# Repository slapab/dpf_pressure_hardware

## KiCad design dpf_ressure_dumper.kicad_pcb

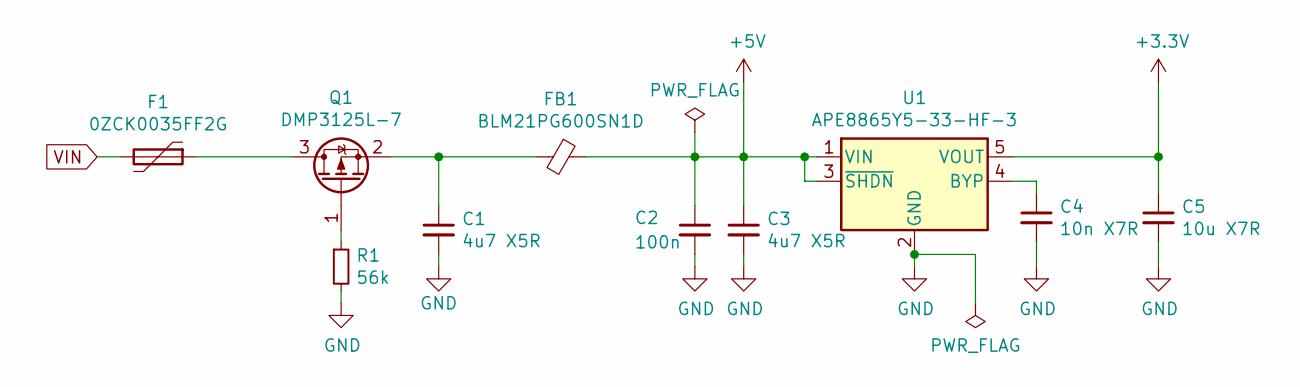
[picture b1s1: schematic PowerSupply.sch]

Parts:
C1, C3: 4u7 X5R; C_0603_1608Metric_Pad1.05x0.95mm_HandSolder
C2: 100n; C_0603_1608Metric
C4: 10n X7R; C_0805_2012Metric
C5: 10u X7R; C_1206_3216Metric
F1: 0ZCK0035FF2G; Fuse_0805_2012Metric_Pad1.15x1.40mm_HandSolder
FB1: BLM21PG600SN1D; L_0805_2012Metric
Q1: DMP3125L-7; SOT-23
R1: 56k; R_0805_2012Metric
U1: APE8865Y5-33-HF-3; SOT-23-5

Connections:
+3V3: C5.1, U1.5 (VOUT); also elsewhere on the board
+5V: C2.1, C3.1, FB1.1, U1.1 (VIN), U1.3 (~SHDN~); also elsewhere on the board
GND: C1.2, C2.2, C3.2, C4.2, C5.2, R1.2, U1.2 (GND); also elsewhere on the board
unnamed: C1.1, FB1.2, Q1.2 (S)
unnamed: C4.1, U1.4 (BYP)
unnamed: F1.1, Q1.3 (D)
unnamed: Q1.1 (G), R1.1
VIN: F1.2; also elsewhere on the board

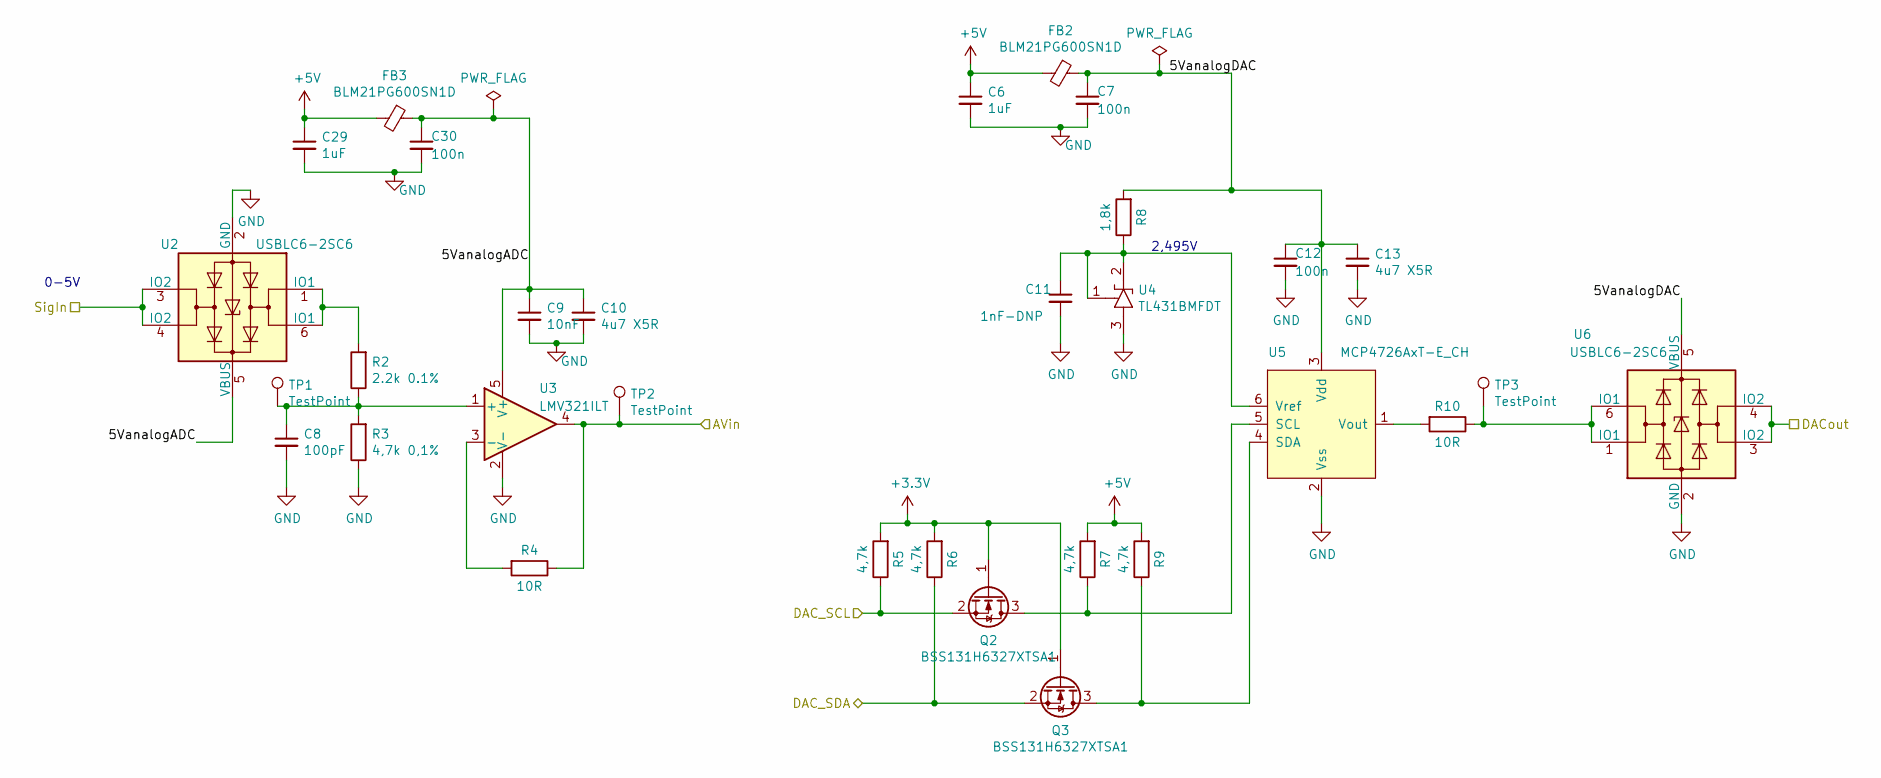
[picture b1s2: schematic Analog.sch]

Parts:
C6, C29: 1uF; C_0603_1608Metric
C7, C12, C30: 100n; C_0603_1608Metric
C8: 100pF; C_0805_2012Metric
C9: 10nF; C_0805_2012Metric
C10, C13: 4u7 X5R; C_0603_1608Metric_Pad1.05x0.95mm_HandSolder
C11: 1nF-DNP; C_0402_1005Metric
FB2, FB3: BLM21PG600SN1D; L_0805_2012Metric
Q2, Q3: BSS131H6327XTSA1; SOT-23
R2: 2.2k 0.1%; R_0603_1608Metric
R3: 4,7k 0,1%; R_0603_1608Metric
R4, R10: 10R; R_0603_1608Metric
R5, R6, R7, R9: 4,7k; R_0805_2012Metric
R8: 1,8k; R_0805_2012Metric
TP1, TP2, TP3: TestPoint; TestPoint_Loop_D1.80mm_Drill1.0mm_Beaded
U2, U6: USBLC6-2SC6; SOT-23-6
U3: LMV321ILT; SOT-23-5
U4: TL431BMFDT; SOT-23
U5: MCP4726AxT-E_CH; SOT-23-6

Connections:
+3V3: Q2.1 (G), Q3.1 (G), R5.2, R6.2; also elsewhere on the board
+5V: C6.1, C29.1, FB2.2, FB3.2, R7.2, R9.2; also elsewhere on the board
/AnalogSections/5VanalogADC: C9.1, C10.1, C30.1, FB3.1, U2.5 (VBUS), U3.5 (V+)
/AnalogSections/5VanalogDAC: C7.1, C12.1, C13.1, FB2.1, R8.2, U5.3 (Vdd), U6.5 (VBUS)
/AnalogSections/AVin: R4.1, TP2.1, U3.4; also elsewhere on the board
/AnalogSections/DAC_SCL: Q2.2 (S), R5.1; also elsewhere on the board
/AnalogSections/DAC_SDA: Q3.2 (S), R6.1; also elsewhere on the board
/Connectors/DAC_OUT: U6.3 (IO2), U6.4 (IO2); also elsewhere on the board
/Connectors/SIG_IN: U2.3 (IO2), U2.4 (IO2); also elsewhere on the board
GND: C6.2, C7.2, C8.2, C9.2, C10.2, C11.2, C12.2, C13.2, C29.2, C30.2, R3.1, U2.2 (GND), U3.2 (V-), U4.3, U5.2 (Vss), U6.2 (GND); also elsewhere on the board
unnamed: C8.1, R2.1, R3.2, TP1.1, U3.1 (+)
unnamed: C11.1, R8.1, U4.1, U4.2, U5.6 (Vref)
unnamed: Q2.3 (D), R7.1, U5.5 (SCL)
unnamed: Q3.3 (D), R9.1, U5.4 (SDA)
unnamed: R2.2, U2.1 (IO1), U2.6 (IO1)
unnamed: R4.2, U3.3 (-)
unnamed: R10.1, TP3.1, U6.1 (IO1), U6.6 (IO1)
unnamed: R10.2, U5.1 (Vout)

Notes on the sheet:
0-5V
2,495V

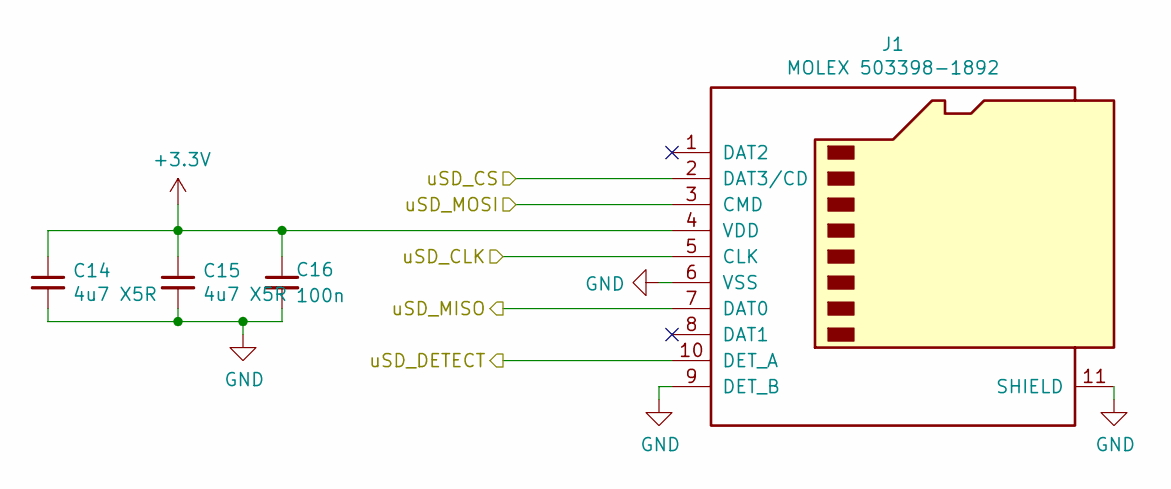
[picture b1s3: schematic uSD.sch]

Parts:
C14, C15: 4u7 X5R; C_0603_1608Metric_Pad1.05x0.95mm_HandSolder
C16: 100n; C_0603_1608Metric
J1: MOLEX 503398-1892; uSD_MOLEX_503398_1892

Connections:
+3V3: C14.1, C15.1, C16.1, J1.4 (VDD); also elsewhere on the board
/nRF51822/uSD_CLK: J1.5 (CLK); also elsewhere on the board
/nRF51822/uSD_CS: J1.2 (DAT3/CD); also elsewhere on the board
/nRF51822/uSD_DETECT: J1.10 (DET_A); also elsewhere on the board
/nRF51822/uSD_MISO: J1.7 (DAT0); also elsewhere on the board
/nRF51822/uSD_MOSI: J1.3 (CMD); also elsewhere on the board
GND: C14.2, C15.2, C16.2, J1.6 (VSS), J1.9 (DET_B), J1.11 (SHIELD); also elsewhere on the board

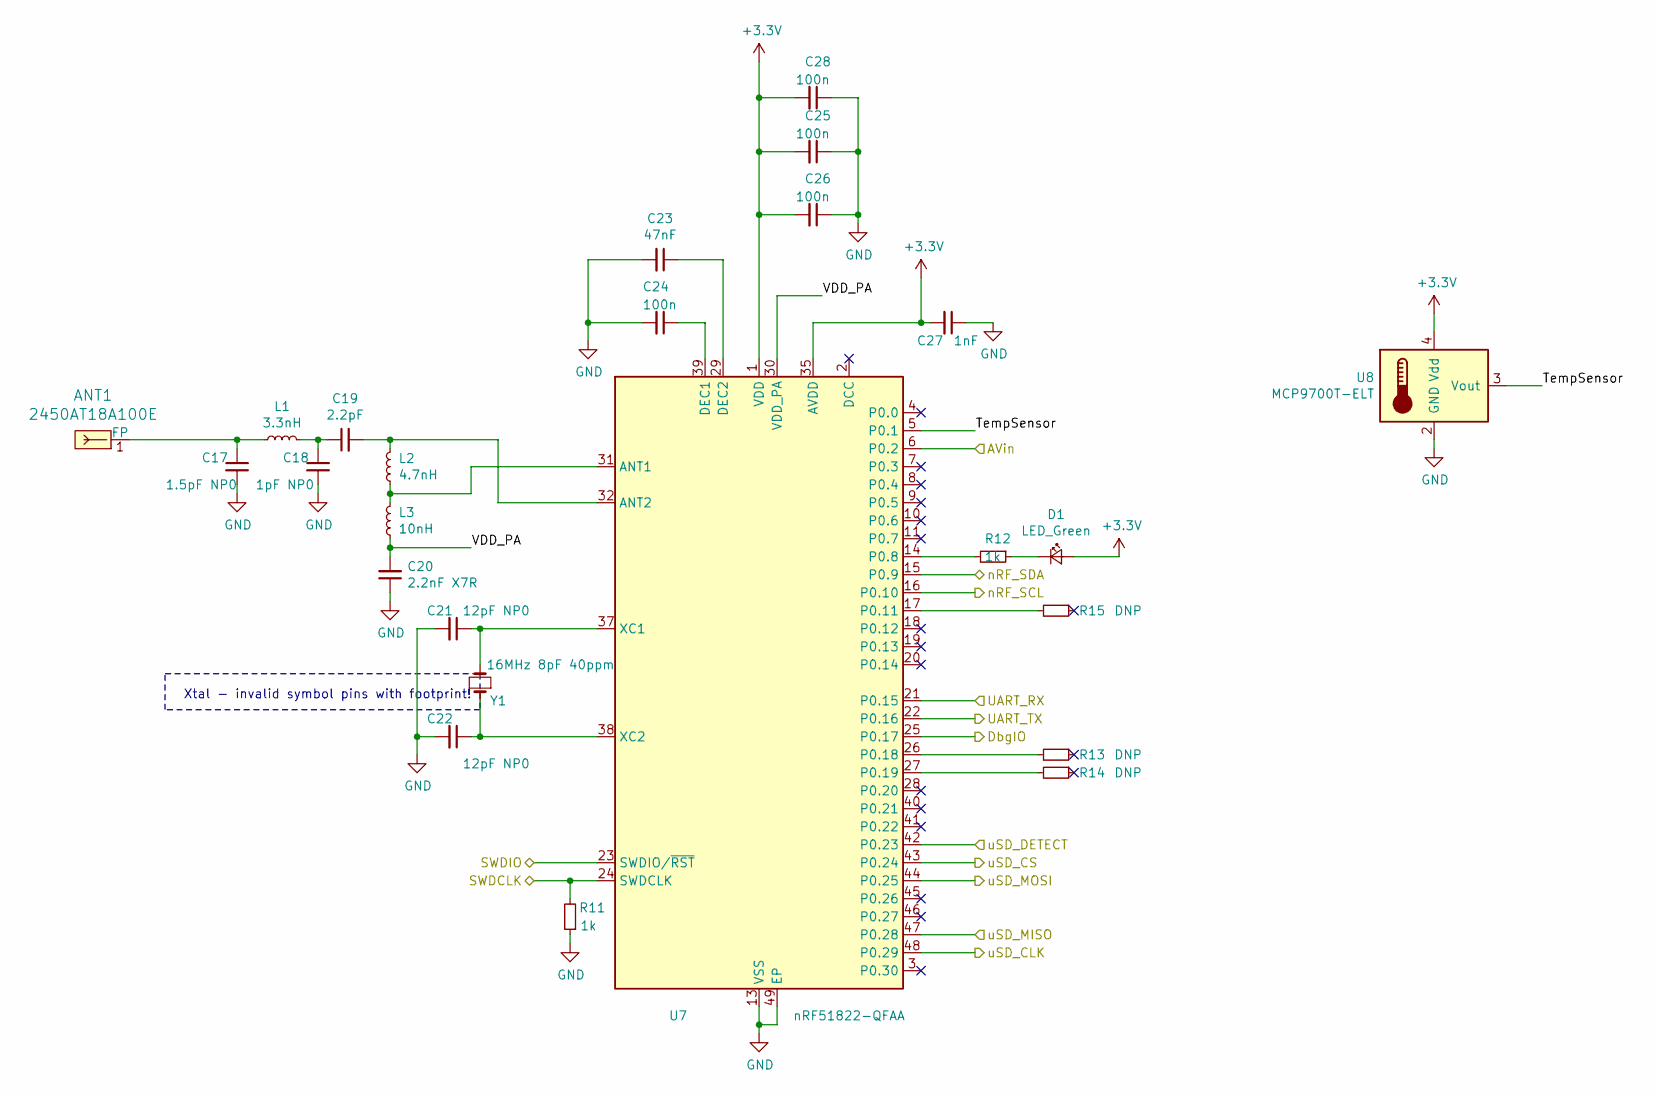
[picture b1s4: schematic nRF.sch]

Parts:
ANT1: 2450AT18A100E; 2.4GHz_ISM_antenna_RFANT8010080A3T; MPN RFANT8010080A3T
C17: 1.5pF NP0; C_0603_1608Metric
C18: 1pF NP0; C_0603_1608Metric
C19: 2.2pF; C_0402_1005Metric
C20: 2.2nF X7R; C_0402_1005Metric
C21, C22: 12pF NP0; C_0402_1005Metric
C23: 47nF; C_0402_1005Metric
C24, C25, C26, C28: 100n; C_0603_1608Metric
C27: 1nF; C_0603_1608Metric
D1: LED_Green; LED_1206_3216Metric
L1: 3.3nH; L_0402_1005Metric
L2: 4.7nH; L_0402_1005Metric
L3: 10nH; L_0402_1005Metric
R11, R12: 1k; R_0603_1608Metric
R13, R14, R15: DNP; R_0603_1608Metric
U7: nRF51822-QFAA; QFN-48-1EP_6x6mm_P0.4mm_EP4.6x4.6mm
U8: MCP9700T-ELT; SOT-353_SC-70-5
Y1: 16MHz 8pF 40ppm; Crystal_SMD_Abracon_ABM10-4Pin_2.5x2.0mm

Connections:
+3V3: C25.2, C26.2, C27.2, C28.2, D1.2 (A), U7.1 (VDD), U7.12 (VDD), U7.35 (AVDD), U7.36 (AVDD), U8.4 (Vdd); also elsewhere on the board
/AnalogSections/AVin: U7.6 (P0.2); also elsewhere on the board
/AnalogSections/DAC_SCL: U7.16 (P0.10); also elsewhere on the board
/AnalogSections/DAC_SDA: U7.15 (P0.9); also elsewhere on the board
/Connectors/SWDCLK: R11.2, U7.24 (SWDCLK); also elsewhere on the board
/Connectors/SWDIO: U7.23 (SWDIO/~RST); also elsewhere on the board
/Connectors/UART_RX: U7.21 (P0.15); also elsewhere on the board
/Connectors/UART_TX: U7.22 (P0.16); also elsewhere on the board
/nRF51822/DbgIO: U7.25 (P0.17); also elsewhere on the board
/nRF51822/TempSensor: U7.5 (P0.1), U8.3 (Vout)
/nRF51822/VDD_PA: C20.2, L3.1, U7.30 (VDD_PA)
/nRF51822/uSD_CLK: U7.48 (P0.29); also elsewhere on the board
/nRF51822/uSD_CS: U7.43 (P0.24); also elsewhere on the board
/nRF51822/uSD_DETECT: U7.42 (P0.23); also elsewhere on the board
/nRF51822/uSD_MISO: U7.47 (P0.28); also elsewhere on the board
/nRF51822/uSD_MOSI: U7.44 (P0.25); also elsewhere on the board
GND: C17.2, C18.2, C20.1, C21.2, C22.2, C23.2, C24.2, C25.1, C26.1, C27.1, C28.1, R11.1, U7.13 (VSS), U7.33 (VSS), U7.34 (VSS), U7.49 (EP), U8.2 (GND); also elsewhere on the board
unnamed: ANT1.1 (FP), C17.1, L1.1
unnamed: C18.1, C19.1, L1.2
unnamed: C19.2, L2.2, U7.32 (ANT2)
unnamed: C21.1, U7.37 (XC1), Y1.2
unnamed: C22.1, U7.38 (XC2), Y1.1
unnamed: C23.1, U7.29 (DEC2)
unnamed: C24.1, U7.39 (DEC1)
unnamed: D1.1 (K), R12.1
unnamed: L2.1, L3.2, U7.31 (ANT1)
unnamed: R12.2, U7.14 (P0.8)
unnamed: R13.2, U7.26 (P0.18)
unnamed: R14.2, U7.27 (P0.19)
unnamed: R15.2, U7.17 (P0.11)

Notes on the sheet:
Xtal - invalid symbol pins with footprint!

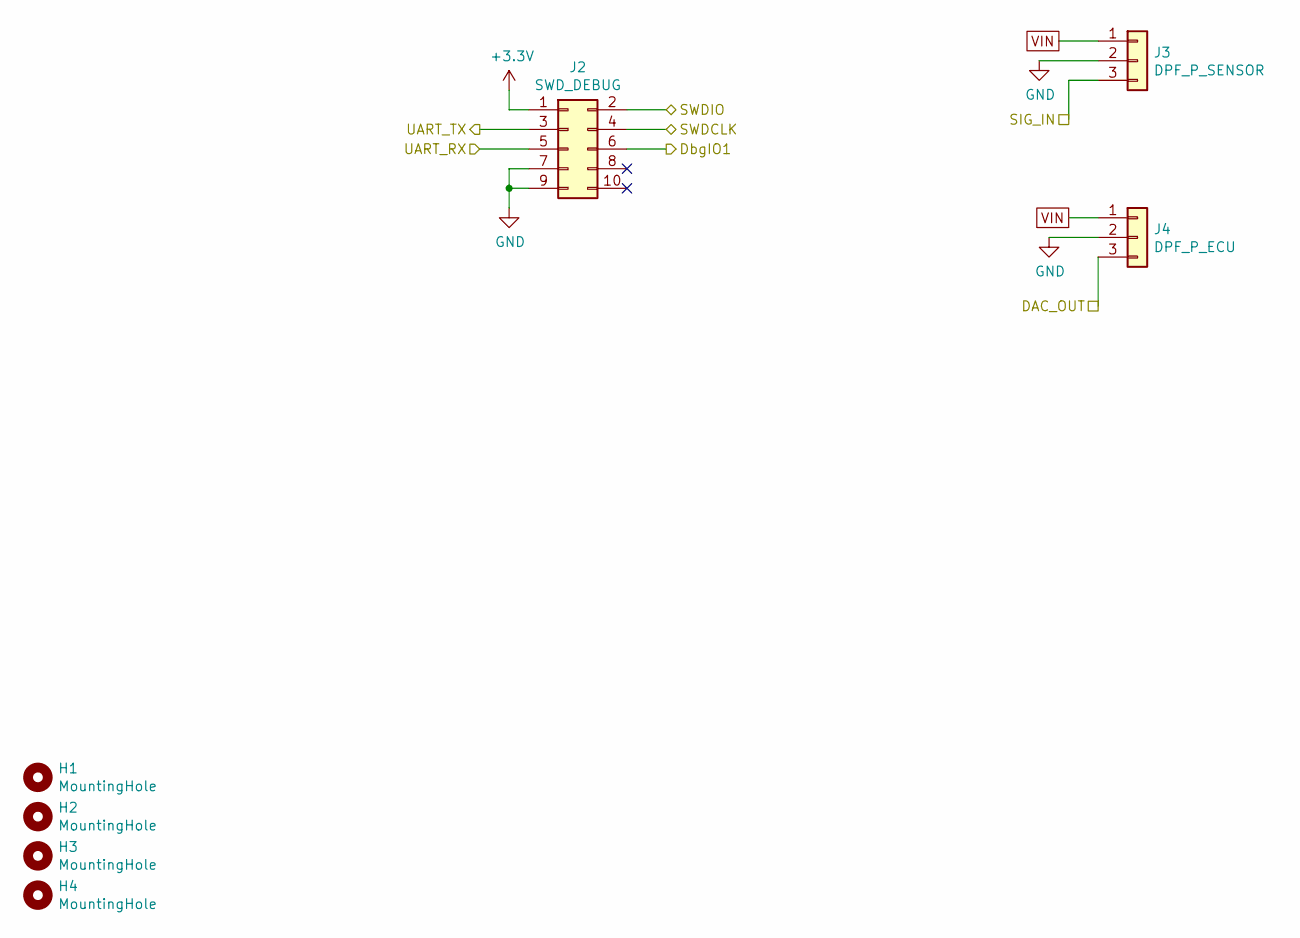
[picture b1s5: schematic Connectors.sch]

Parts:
H1, H2, H3, H4: MountingHole; MountingHole_2.5mm
J2: SWD_DEBUG; PinHeader_2x05_P1.27mm_Vertical_SMD
J3: DPF_P_SENSOR; JST_EH_B3B-EH-A_1x03_P2.50mm_Vertical
J4: DPF_P_ECU; JST_EH_B3B-EH-A_1x03_P2.50mm_Vertical

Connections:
+3V3: J2.1; also elsewhere on the board
/Connectors/DAC_OUT: J4.3; also elsewhere on the board
/Connectors/SIG_IN: J3.3; also elsewhere on the board
/Connectors/SWDCLK: J2.4; also elsewhere on the board
/Connectors/SWDIO: J2.2; also elsewhere on the board
/Connectors/UART_RX: J2.5; also elsewhere on the board
/Connectors/UART_TX: J2.3; also elsewhere on the board
/nRF51822/DbgIO: J2.6; also elsewhere on the board
GND: J2.7, J2.9, J3.2, J4.2; also elsewhere on the board
VIN: J3.1, J4.1; also elsewhere on the board

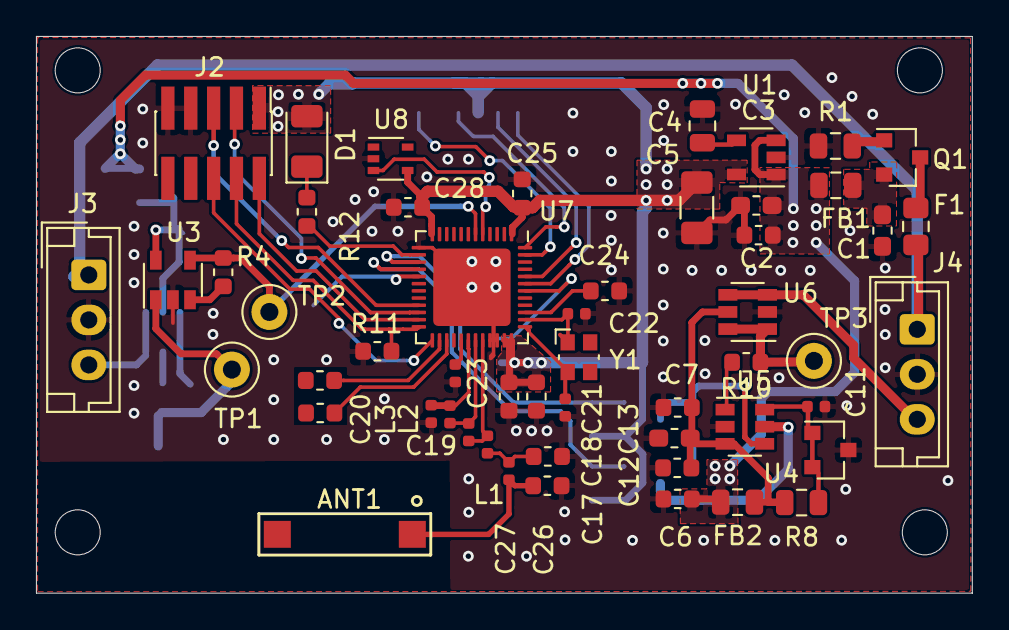
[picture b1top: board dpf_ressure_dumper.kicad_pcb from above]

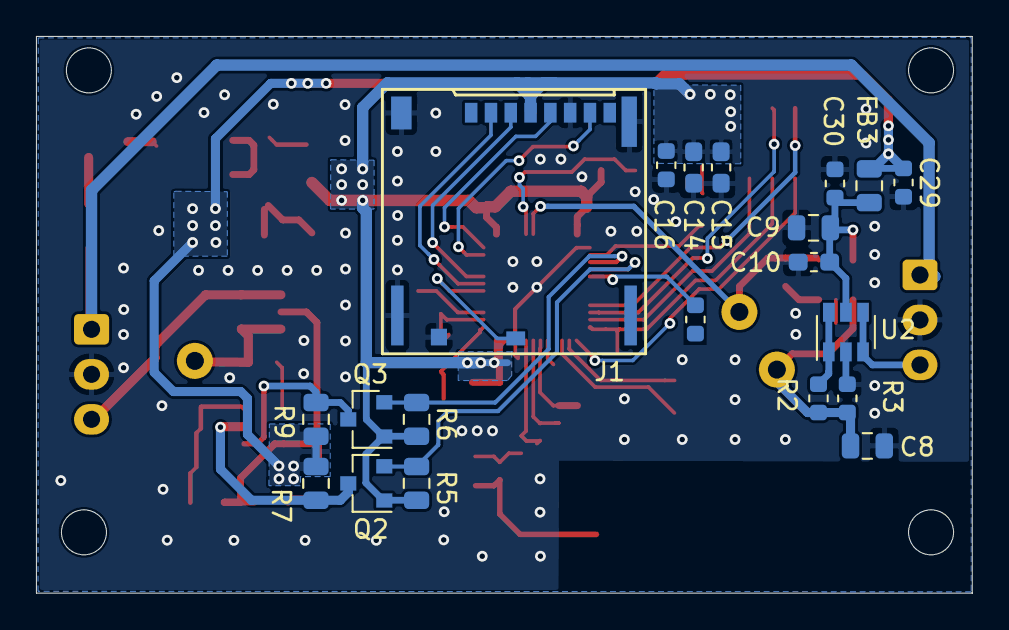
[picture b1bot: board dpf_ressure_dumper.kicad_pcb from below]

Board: 2 copper layers, 52.0 x 30.9 mm, 77 parts (20 on the bottom side), 48 nets.

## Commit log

2020-04-13 Version 1.0x
